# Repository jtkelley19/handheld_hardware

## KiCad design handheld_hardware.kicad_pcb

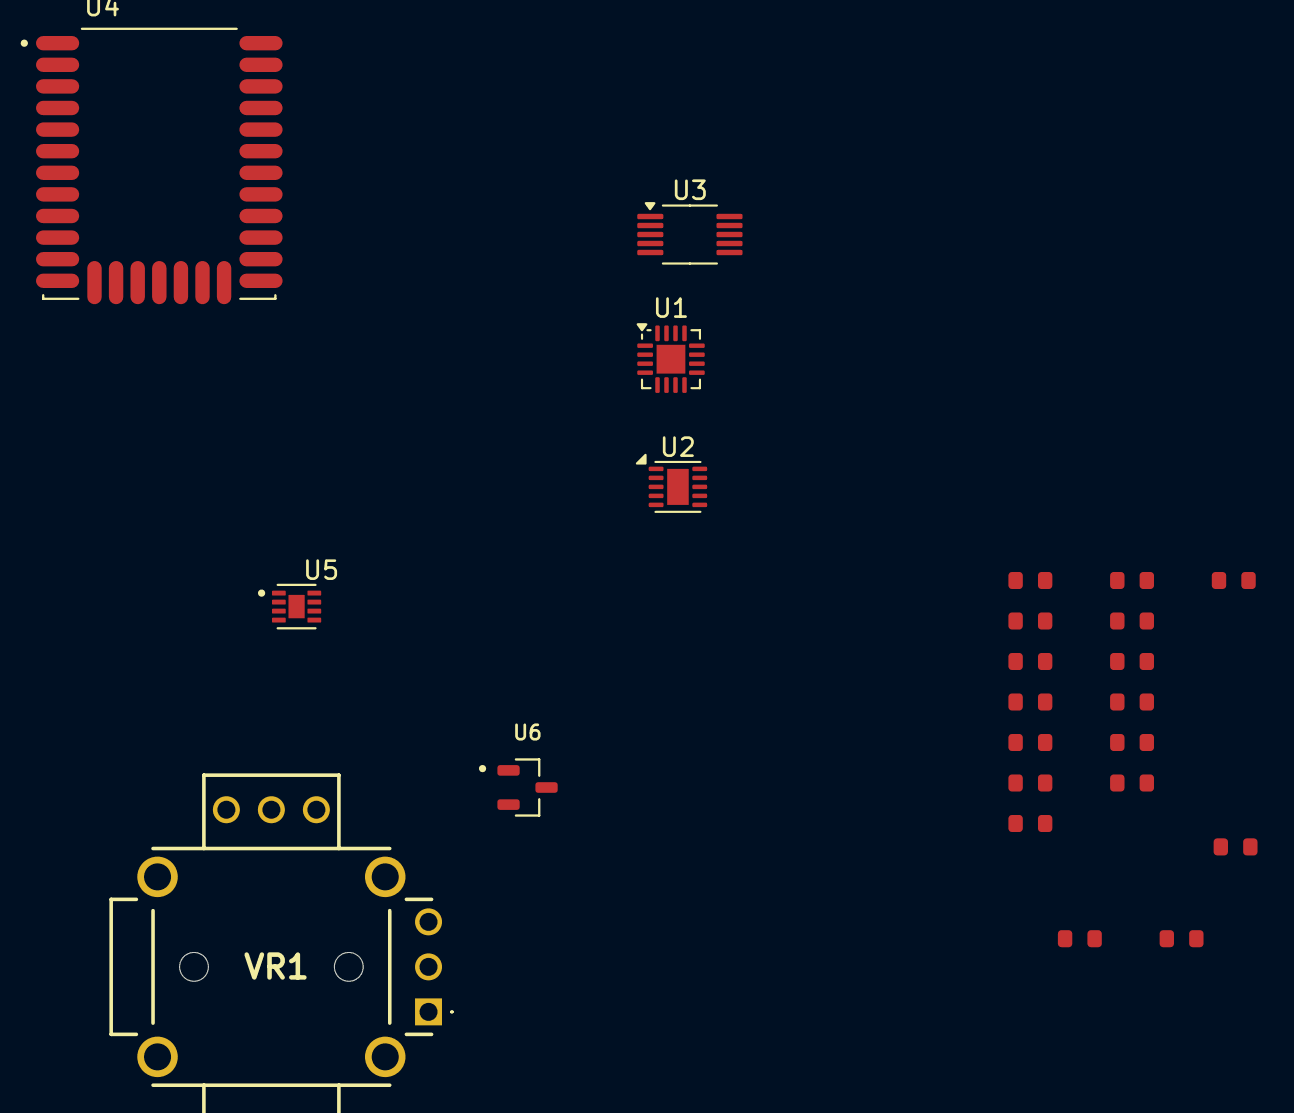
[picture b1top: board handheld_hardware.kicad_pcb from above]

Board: 2 copper layers, 24 parts (0 on the bottom side), 24 nets, no tracks yet.

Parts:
R1, R2: 2.2k; R_0603
R3, R4, R7, R8, R9, R14, R15: 10k; R_0603
R5: 1.18k?; R_0603
R6: 1.13k?; R_0603
R10, R11: 0R; R_0603
R12: OR; R_0603
R13, R16, R17: DNP; R_0603
U1: BQ24075RGT; VQFN-16-1EP_3x3mm_P0.5mm_EP1.6x1.6mm
U2: TPS63031DSK; WSON-10-1EP_2.5x2.5mm_P0.5mm_EP1.2x2mm
U3: DRV2605LDGS; VSSOP-10_3x3mm_P0.5mm
U4: BGM220PC22HNA2; MODULE_BGM220PC22HNA2
U5: MAX17048G_T10; SON50P200X200X80-9N
U6: DRV5053CAQDBZR; SOT95P237X112-3N
VR1: RKJXV1224005

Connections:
+3V3: R1.1, R2.1, R16.2, R17.2, U2.1 (VOUT), U2.10 (FB), U3.10 (VDD), U4.13 (VDD), U6.1 (VCC), VR1.A3 (CW_1), VR1.B3 (CW_2)
+5V: R13.2, U1.13 (IN)
/MCU/Board_ID_0: R14.2, R16.1, U4.19 (PD02)
/MCU/Board_ID_1: R15.2, R17.1, U4.18 (PD03)
/MCU/MCU_Rx: R11.1, U4.14 (PA05)
/MCU/MCU_Tx: R10.2, U4.15 (PA06)
/MCU/Trigger: U4.11 (PA04), U6.2 (OUT)
/MCU/X_Axis: U4.16 (PA07), VR1.A2 (WIPER_1)
/MCU/Y_Axis: U4.17 (PA08), VR1.B2 (WIPER_2)
/Power/VBAT: U1.2 (BAT), U1.3 (BAT), U5.2 (CELL), U5.3 (VDD)
BATT_ALERT: R8.1, U4.25 (PC03), U5.5 (~ALERT)
CHG_STATUS: R4.1, U1.9 (~CHG), U4.27 (PC05)
GND: R5.2, R6.1, R7.1, R9.1, R14.1, R15.1, U1.4 (~CE), U1.6 (EN1), U1.8 (VSS), U1.14 (TMR), U1.17 (VSS), U2.3 (PGND), U2.9 (GND), U2.11 (PGND), U3.8 (GND), U4.1 (GND), U4.12 (GND__1), U4.20 (GND__2), U4.31 (GND__3), U5.1 (CTG), U5.4 (GND), U5.6 (QSTRT), U5.9 (EP), U6.3 (GND), VR1.1 (MH1), VR1.2 (MH2), VR1.3 (MH3), VR1.4 (MH4), VR1.A1 (CCW_1), VR1.B1 (CCW_2)
Haptic_Enable: U3.5 (EN), U4.28 (PC06)
unnamed: R5.1, U1.12 (ILIM)
unnamed: R6.2, U1.16 (ISET)
unnamed: R7.2, U1.15 (SYSOFF)
unnamed: U2.6 (EN), U2.7 (PS/SYNC), U2.8 (VINA)
unnamed: R12.1, R13.1, U2.5 (VIN)
unnamed: R9.2, U3.4 (IN/TRIG)
PGOOD: R3.1, U1.7 (~PGOOD), U4.26 (PC04)
SCL: R2.2, U3.2 (SCL), U4.23 (PC01), U5.7 (SCL)
SDA: R1.2, U3.3 (SDA), U4.22 (PC00), U5.8 (SDA)
VBUS: R3.2, R4.2, R8.2, R12.2, U1.5 (EN2), U1.10 (OUT), U1.11 (OUT)

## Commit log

2026-03-23 Continued work, intial schematic finished
